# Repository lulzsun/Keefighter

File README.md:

# Keefighter
Keyboard-styled gamepad controller designed for fighting games. Made to fit into 60% keyboard cases.

## License

The Keefighter controller is licensed under [Creative Commons Attribution-NonCommercial 4.0 International License](https://creativecommons.org/licenses/by-nc/4.0).

This PCB design may be freely reproduced, modified, and manufactured for personal use only. If you would like to use this design commercially please reach out to request permission.

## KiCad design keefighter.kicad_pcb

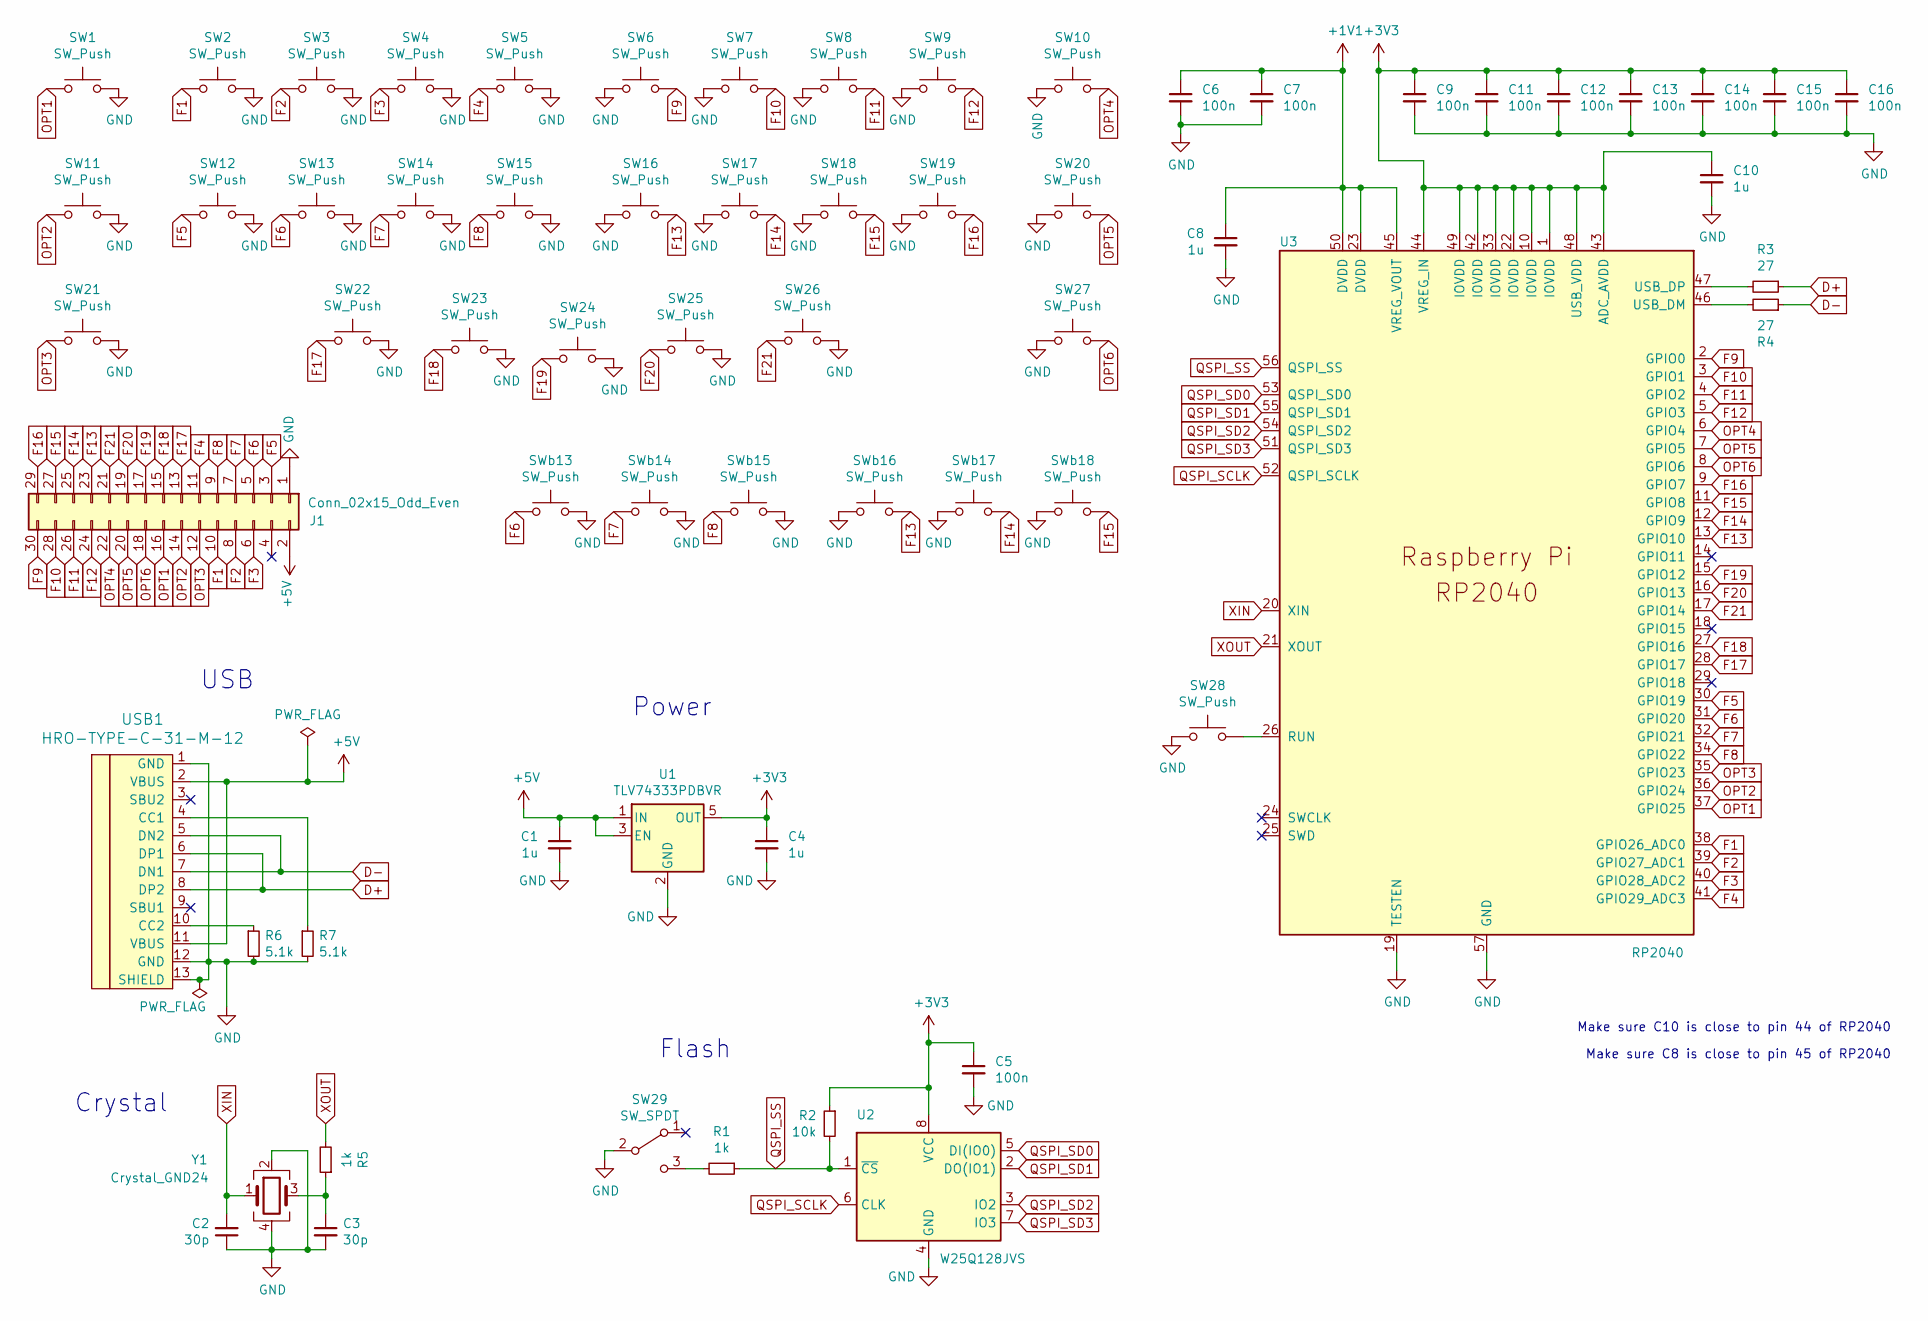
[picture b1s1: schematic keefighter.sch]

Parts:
C1, C4, C8, C10: 1u; C_0603_1608Metric; LCSC C15849
C2, C3: 30p; C_0603_1608Metric; LCSC C22397
C5, C6, C7, C9, C11, C12, C13, C14, C15, C16: 100n; C_0603_1608Metric; LCSC C14663
J1: Conn_02x15_Odd_Even; PinHeader_2x15_P2.54mm_Vertical
R1, R5: 1k; R_0603_1608Metric; LCSC C21190
R2: 10k; R_0603_1608Metric; LCSC C25804
R3, R4: 27; R_0603_1608Metric; LCSC C25190
R6, R7: 5.1k; R_0603_1608Metric; LCSC C23186
SW1, SW2, SW3, SW4, SW5, SW6, SW7, SW8, SW9, SW10, SW11, SW12, SW13, SW14, SW15, SW16, SW17, SW18, SW19, SW20, SW21, SW22, SW23, SW24, SW25, SW26, SW27: SW_Push; Kailh_socket_PG1350
SW28: SW_Push; SW_Push_SPST_NO_Alps_SKRK; LCSC C115357
SW29: SW_SPDT; SW_SPDT_PCM12; LCSC C431541
SWb13, SWb14, SWb15, SWb16, SWb17, SWb18: SW_Push; Kailh_socket_PG1350
U1: TLV74333PDBVR; SOT-23-5; LCSC C408972
U2: W25Q128JVS; SOIC-8_5.23x5.23mm_P1.27mm; LCSC C97521
U3: RP2040; RP2040-QFN-56; LCSC C2040
USB1: HRO-TYPE-C-31-M-12; HRO-TYPE-C-31-M-12-Assembly; LCSC C165948
Y1: Crystal_GND24; Crystal_SMD_3225-4Pin_3.2x2.5mm; LCSC C9002

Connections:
+1V1: C6.1, C7.1, C8.1, U3.23 (DVDD), U3.45 (VREG_VOUT), U3.50 (DVDD)
+3V3: C4.1, C5.1, C9.1, C10.1, C11.1, C12.1, C13.1, C14.1, C15.1, C16.1, R2.1, U1.5 (OUT), U2.8 (VCC), U3.1 (IOVDD), U3.10 (IOVDD), U3.22 (IOVDD), U3.33 (IOVDD), U3.42 (IOVDD), U3.43 (ADC_AVDD), U3.44 (VREG_IN), U3.48 (USB_VDD), U3.49 (IOVDD)
+5V: C1.1, J1.2, U1.1 (IN), U1.3 (EN), USB1.2 (VBUS), USB1.11 (VBUS)
D+: R3.1, USB1.6 (DP1), USB1.8 (DP2)
D-: R4.1, USB1.5 (DN2), USB1.7 (DN1)
F1: J1.10, SW2.1, U3.38 (GPIO26_ADC0)
F2: J1.8, SW3.1, U3.39 (GPIO27_ADC1)
F3: J1.6, SW4.1, U3.40 (GPIO28_ADC2)
F4: J1.11, SW5.1, U3.41 (GPIO29_ADC3)
F5: J1.3, SW12.1, U3.30 (GPIO19)
F6: J1.5, SW13.1, SWb13.1, U3.31 (GPIO20)
F7: J1.7, SW14.1, SWb14.1, U3.32 (GPIO21)
F8: J1.9, SW15.1, SWb15.1, U3.34 (GPIO22)
F9: J1.30, SW6.2, U3.2 (GPIO0)
F10: J1.28, SW7.2, U3.3 (GPIO1)
F11: J1.26, SW8.2, U3.4 (GPIO2)
F12: J1.24, SW9.2, U3.5 (GPIO3)
F13: J1.23, SW16.2, SWb16.2, U3.13 (GPIO10)
F14: J1.25, SW17.2, SWb17.2, U3.12 (GPIO9)
F15: J1.27, SW18.2, SWb18.2, U3.11 (GPIO8)
F16: J1.29, SW19.2, U3.9 (GPIO7)
F17: J1.13, SW22.1, U3.28 (GPIO17)
F18: J1.15, SW23.1, U3.27 (GPIO16)
F19: J1.17, SW24.1, U3.15 (GPIO12)
F20: J1.19, SW25.1, U3.16 (GPIO13)
F21: J1.21, SW26.1, U3.17 (GPIO14)
GND: C1.2, C2.1, C3.2, C4.2, C5.2, C6.2, C7.2, C8.2, C9.2, C10.2, C11.2, C12.2, C13.2, C14.2, C15.2, C16.2, J1.1, R6.2, R7.2, SW1.2, SW2.2, SW3.2, SW4.2, SW5.2, SW6.1, SW7.1, SW8.1, SW9.1, SW10.1, SW11.2, SW12.2, SW13.2, SW14.2, SW15.2, SW16.1, SW17.1, SW18.1, SW19.1, SW20.1, SW21.2, SW22.2, SW23.2, SW24.2, SW25.2, SW26.2, SW27.1, SW28.1, SW29.2 (B), SWb13.2, SWb14.2, SWb15.2, SWb16.1, SWb17.1, SWb18.1, U1.2 (GND), U2.4 (GND), U3.19 (TESTEN), U3.57 (GND), USB1.1 (GND), USB1.12 (GND), USB1.13 (SHIELD), Y1.2, Y1.4
unnamed: C3.1, R5.1, Y1.3
unnamed: R1.2, SW29.3 (C)
unnamed: R3.2, U3.47 (USB_DP)
unnamed: R4.2, U3.46 (USB_DM)
unnamed: R6.1, USB1.10 (CC2)
unnamed: R7.1, USB1.4 (CC1)
unnamed: SW28.2, U3.26 (RUN)
OPT1: J1.16, SW1.1, U3.37 (GPIO25)
OPT2: J1.14, SW11.1, U3.36 (GPIO24)
OPT3: J1.12, SW21.1, U3.35 (GPIO23)
OPT4: J1.22, SW10.2, U3.6 (GPIO4)
OPT5: J1.20, SW20.2, U3.7 (GPIO5)
OPT6: J1.18, SW27.2, U3.8 (GPIO6)
QSPI_SCLK: U2.6 (CLK), U3.52 (QSPI_SCLK)
QSPI_SD0: U2.5 (DI(IO0)), U3.53 (QSPI_SD0)
QSPI_SD1: U2.2 (DO(IO1)), U3.55 (QSPI_SD1)
QSPI_SD2: U2.3 (IO2), U3.54 (QSPI_SD2)
QSPI_SD3: U2.7 (IO3), U3.51 (QSPI_SD3)
QSPI_SS: R1.1, R2.2, U2.1 (~CS), U3.56 (QSPI_SS)
XIN: C2.2, U3.20 (XIN), Y1.1
XOUT: R5.2, U3.21 (XOUT)

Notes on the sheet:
Make sure C10 is close to pin 44 of RP2040
Crystal
Power
USB
Make sure C8 is close to pin 45 of RP2040
Flash

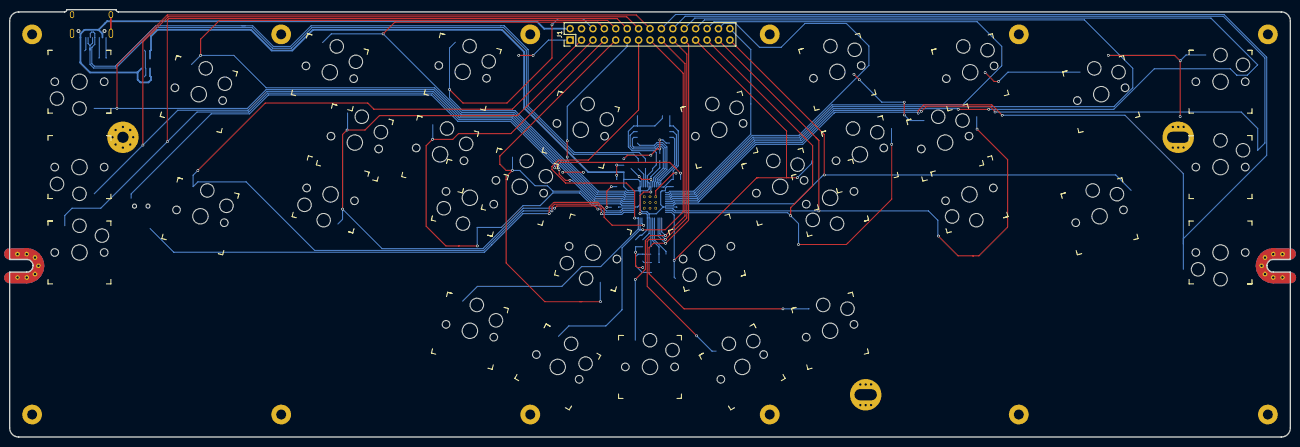
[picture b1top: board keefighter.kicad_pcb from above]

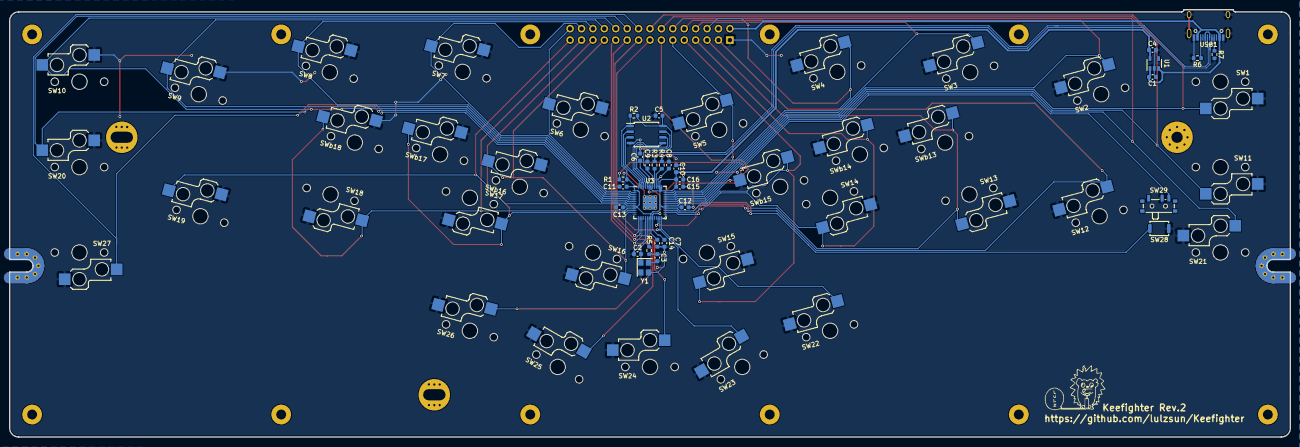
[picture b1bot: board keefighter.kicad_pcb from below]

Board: 2 copper layers, 285.0 x 95.1 mm, 65 parts (31 on the bottom side), 48 nets.

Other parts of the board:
Ref**: Val**; logo

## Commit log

2021-05-25 Local to remote commit
2021-11-03 asdfasf
2021-11-03 Fixed routing issues with matrix
2022-01-25 Use components/schematics from flatbox
    jfedor2's flatbox will be used as a guide for building the Keefighter
2022-02-26 JLCPCB ready for prod
2022-11-07 Change license to CC-BY-NC-4.0
